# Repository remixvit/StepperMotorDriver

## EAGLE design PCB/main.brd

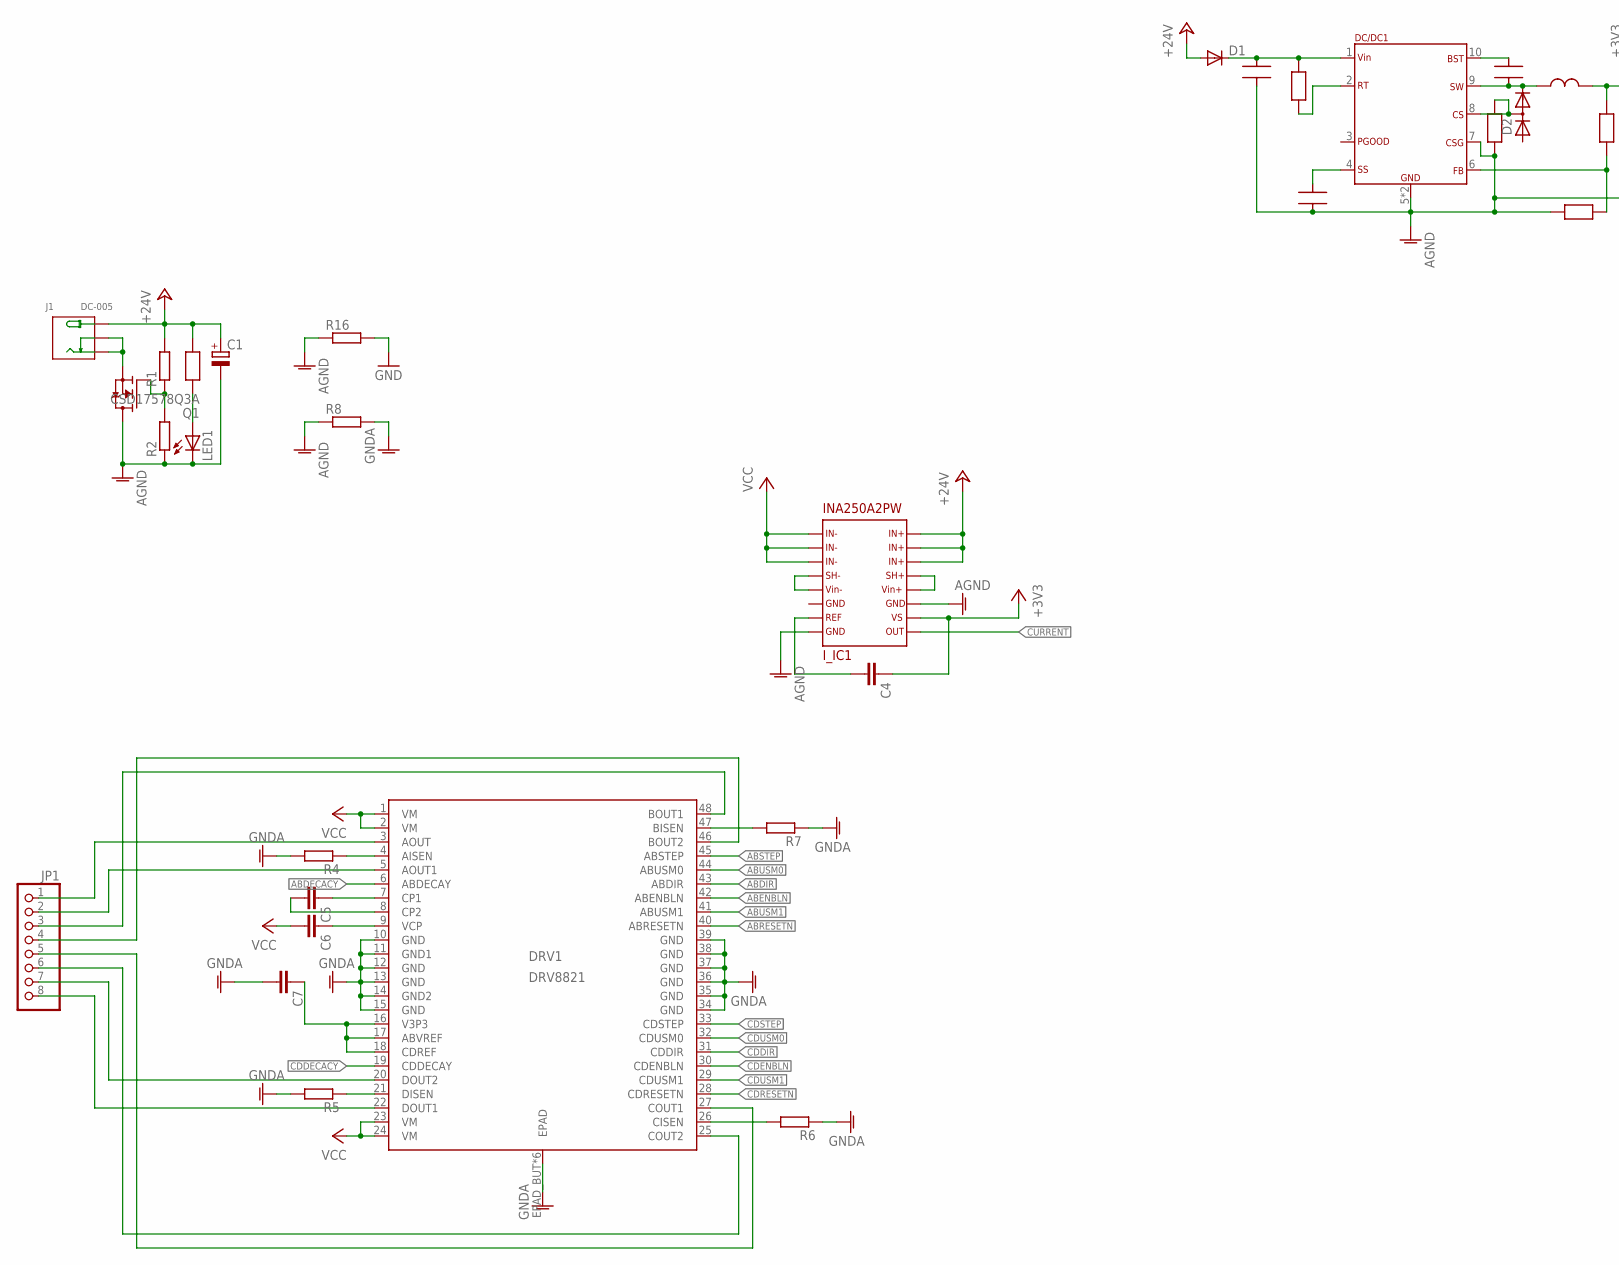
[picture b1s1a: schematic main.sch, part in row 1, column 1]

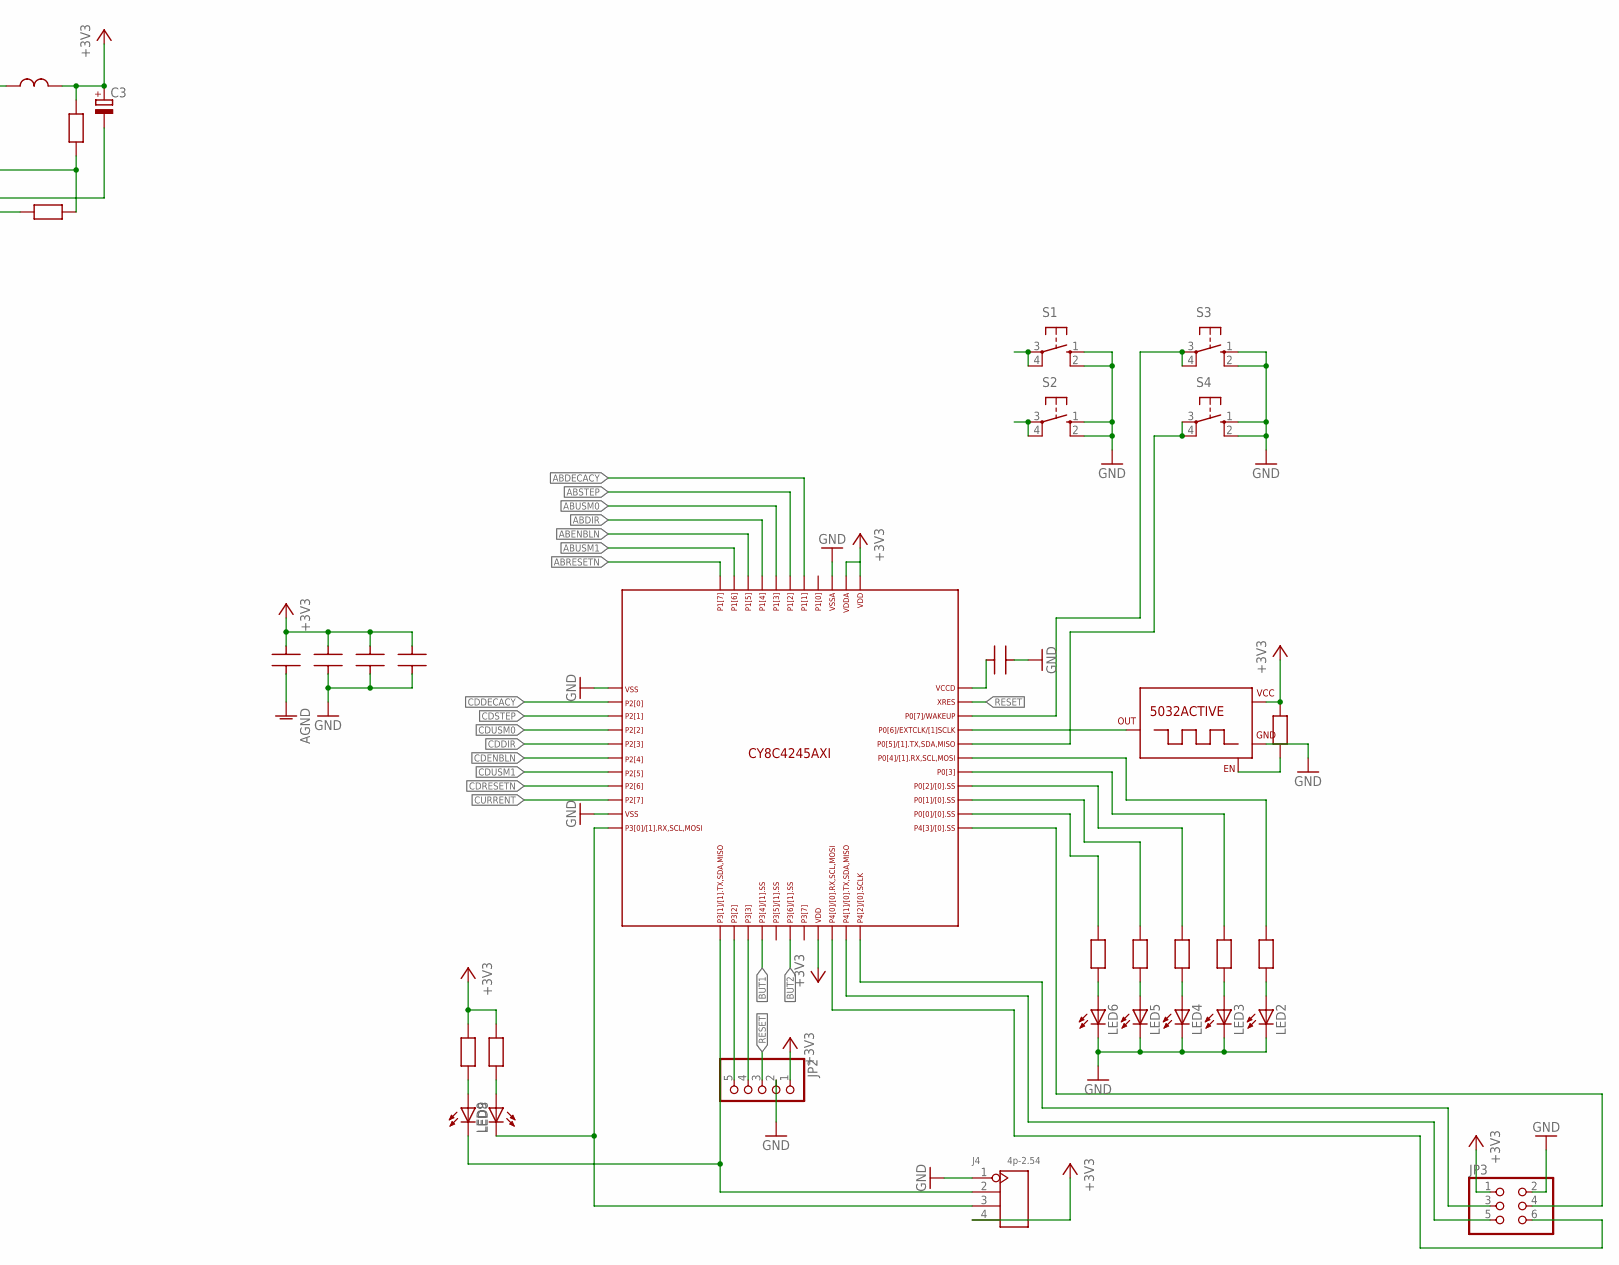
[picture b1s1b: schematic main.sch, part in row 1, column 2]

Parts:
C1, C3: CPOL-EUSMCD; SMC_D
C2, C8, C9, C10, C11, C12, C13, C14: CAP0603; C0603
C4, C5, C6, C7: C-EUC0805; C0805
D1: DIODE-DO-214AC; DO-214AC
D2: DIODE_2CACA-SOT23; SOT23
DC/DC1: LM25011; HVSSOP-10
DRV1: DRV8821; HTSSOP_48
I_IC1: INA250A2PW; SSOP16
J1: DC-005; DCJ3P-14.2X11.0X9.0MM
J4: 4p-2.54; H4-2.54
JP1: PINHD-1X8; 1X08
JP2: PINHD-1X5; 1X05
JP3: PINHD-2X3; 2X03
L1: L0603
LED1: LEDCHIP-LED0805; CHIP-LED0805
LED2, LED3, LED4, LED5, LED6, LED8, LED9: LEDCHIP-LED0603; CHIP-LED0603
Q1: CSD17578Q3A; VSONP8
R1, R2, R4, R5, R6, R7, R8, R16: R-EU_M0805; M0805
R3, R9, R10, R11, R12, R13, R14, R15, R17, R18, R19, R20, R21: RES0603; R0603
S1, S2, S3, S4: 10-XX; B3F-10XX
U$1: CY8C4245; TQFP44_CY_LOGO
U$4: 5032ACTIVE; 5030A

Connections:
+3V3: C3.+, C4.1, C10.1, C12.1, C13.1, C14.1, I_IC1.P$10, J4.4, JP2.1, JP3.1, L1.2, R14.2, R15.2, R17.1, R21.1, U$1.19, U$1.34, U$1.35, U$4.4 (+5V)
+24V: C1.+, D1.A, I_IC1.P$14, I_IC1.P$15, I_IC1.P$16, J1.+, R1.2, R3.2
ABDECACY: DRV1.6 (ABDECAY), U$1.38
ABDIR: DRV1.43 (ABDIR), U$1.41
ABENBLN: DRV1.42 (ABENBLN), U$1.42
ABRESETN: DRV1.40 (ABRESETN), U$1.44
ABSTEP: DRV1.45 (ABSTEP), U$1.39
ABUSM0: DRV1.44 (ABUSM0), U$1.40
ABUSM1: DRV1.41 (ABUSM1), U$1.43
AGND: C1.-, C2.1, C3.-, C8.1, C14.2, DC/DC1.5, DC/DC1.7, DC/DC1.EPAD (5), I_IC1.P$8, I_IC1.P$11, LED1.C, Q1.D1 (D), Q1.D2 (D), Q1.D3 (D), Q1.D4 (D), Q1.D5 (D), R2.1, R8.1, R16.1, R19.1, R20.2
BUT1: S1.3, S1.4 (P1), U$1.15
BUT2: S2.3, S2.4 (P1), U$1.17
CDDECACY: DRV1.19 (CDDECAY), U$1.2
CDDIR: DRV1.31 (CDDIR), U$1.5
CDENBLN: DRV1.30 (CDENBLN), U$1.6
CDRESETN: DRV1.28 (CDRESETN), U$1.8
CDSTEP: DRV1.33 (CDSTEP), U$1.3
CDUSM0: DRV1.32 (CDUSM0), U$1.4
CDUSM1: DRV1.29 (CDUSM1), U$1.7
CURRENT: I_IC1.P$9, U$1.9
GND: C10.2, C11.1, C12.2, C13.2, J4.1, JP2.2, JP3.2, LED2.C, LED3.C, LED4.C, LED5.C, LED6.C, R16.2, S1.1 (S), S1.2 (S1), S2.1 (S), S2.2 (S1), S3.1 (S), S3.2 (S1), S4.1 (S), S4.2 (S1), U$1.1, U$1.10, U$1.36, U$4.2 (GND)
GNDA: C7.2, DRV1.10 (GND), DRV1.11 (GND1), DRV1.12 (GND), DRV1.13 (GND), DRV1.14 (GND2), DRV1.15 (GND), DRV1.34 (GND), DRV1.35 (GND), DRV1.36 (GND), DRV1.37 (GND), DRV1.38 (GND), DRV1.39 (GND), DRV1.EPAD_BUT (EPAD), DRV1.EPAD_TOP (EPAD), DRV1.EPAD_VIA1 (EPAD), DRV1.EPAD_VIA2 (EPAD), DRV1.EPAD_VIA3 (EPAD), DRV1.EPAD_VIA4 (EPAD), R4.2, R5.2, R6.1, R7.1, R8.2
unnamed: J1.-1 (-), J1.-2 (CDN), Q1.S1 (S), Q1.S2 (S), Q1.S3 (S)
unnamed: C2.2, D1.C, DC/DC1.1, R18.2
unnamed: Q1.G, R1.1, R2.2
unnamed: LED1.A, R3.1
unnamed: C8.2, DC/DC1.4
unnamed: DRV1.3 (AOUT), JP1.1
unnamed: DRV1.5 (AOUT1), JP1.2
unnamed: DRV1.22 (DOUT1), JP1.8
unnamed: DRV1.20 (DOUT2), JP1.7
unnamed: DRV1.48 (BOUT1), JP1.3
unnamed: DRV1.46 (BOUT2), JP1.4
unnamed: DRV1.25 (COUT2), JP1.6
unnamed: DRV1.27 (COUT1), JP1.5
unnamed: I_IC1.P$4, I_IC1.P$5
unnamed: I_IC1.P$12, I_IC1.P$13
unnamed: C4.2, I_IC1.P$7
unnamed: C5.1, DRV1.7 (CP1)
unnamed: C5.2, DRV1.8 (CP2)
unnamed: C6.1, DRV1.9 (VCP)
unnamed: JP3.4, U$1.23
unnamed: DRV1.4 (AISEN), R4.1
unnamed: DRV1.21 (DISEN), R5.1
unnamed: DRV1.26 (CISEN), R6.2
unnamed: DRV1.47 (BISEN), R7.2
unnamed: JP3.3, U$1.22
unnamed: DC/DC1.2, R18.1
unnamed: C7.1, DRV1.16 (V3P3), DRV1.17 (ABVREF), DRV1.18 (CDREF)
unnamed: R13.2, U$1.28
unnamed: R12.2, U$1.27
unnamed: R11.2, U$1.26
unnamed: R10.2, U$1.25
unnamed: R9.2, U$1.24
unnamed: JP3.5, U$1.21
unnamed: S3.3, S3.4 (P1), U$1.31
unnamed: S4.3, S4.4 (P1), U$1.29
unnamed: JP3.6, U$1.20
unnamed: LED6.A, R9.1
unnamed: LED5.A, R10.1
unnamed: LED4.A, R11.1
unnamed: LED3.A, R12.1
unnamed: LED2.A, R13.1
unnamed: J4.2, LED8.C, U$1.12
unnamed: J4.3, LED9.C, U$1.11
unnamed: R17.2, U$4.1 (EN)
unnamed: LED9.A, R15.1
unnamed: LED8.A, R14.1
unnamed: C9.2, DC/DC1.10
unnamed: C9.1, D2.2 (C), DC/DC1.9, L1.1
unnamed: JP2.5, U$1.13
unnamed: JP2.4, U$1.14
unnamed: U$1.30, U$4.3 (OUT)
unnamed: D2.3 (AC), DC/DC1.8, R19.2
unnamed: C11.2, U$1.33
unnamed: DC/DC1.6, R20.1, R21.2
RESET: JP2.3, U$1.32
VCC: C6.2, DRV1.1 (VM), DRV1.2 (VM), DRV1.23 (VM), DRV1.24 (VM), I_IC1.P$1, I_IC1.P$2, I_IC1.P$3

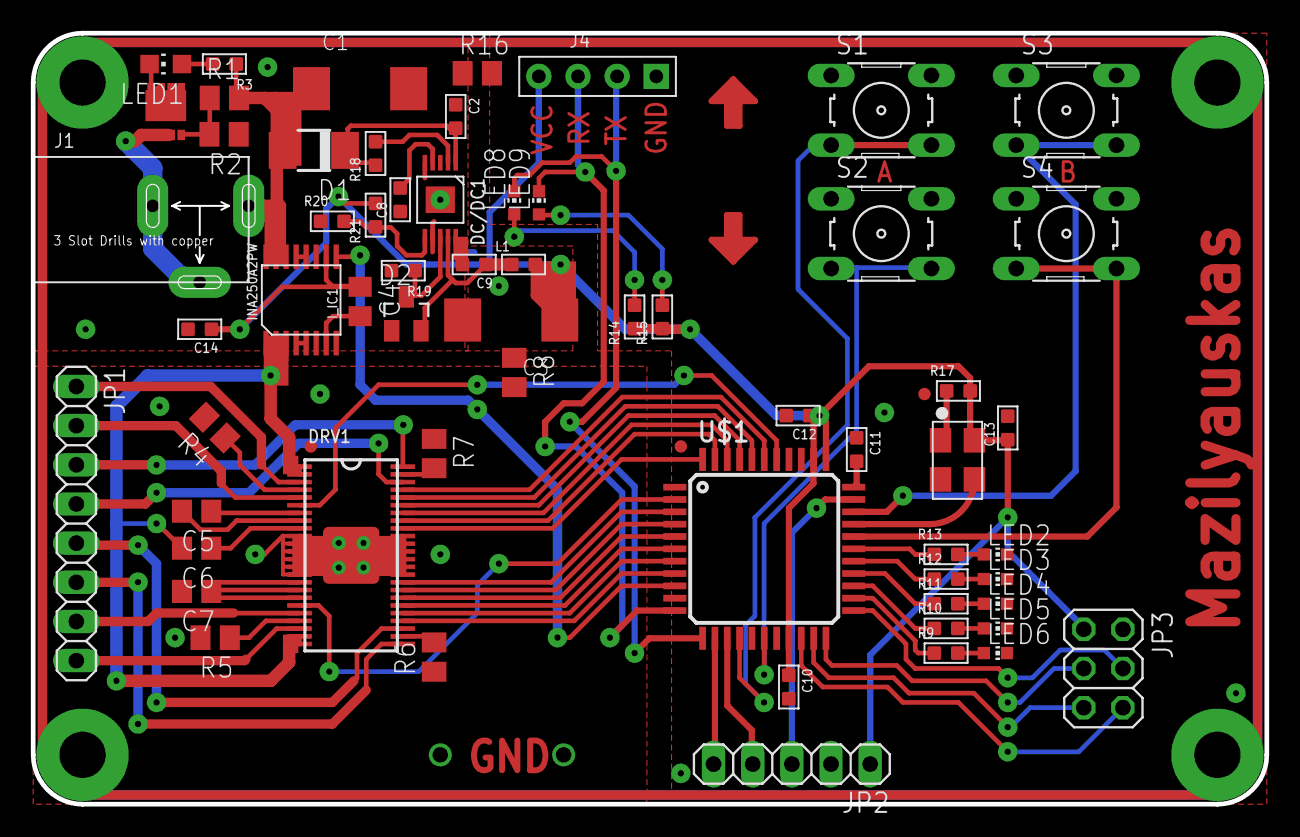
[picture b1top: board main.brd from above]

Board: 2 copper layers, 80.0 x 50.0 mm, 61 parts (0 on the bottom side), 78 nets.

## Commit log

2015-11-25 Add power syply & steper motor driver
2015-11-25 File menegment
2015-11-26 Create PSoC project
2015-12-17 BugFix
2016-02-17 Reroute PCB
2016-02-20 Bug Fix/ Final Version
2016-02-24 Change Power Regulator
